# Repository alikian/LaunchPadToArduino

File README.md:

# LaunchPadToArduino
This a Arduino to LaunchPad adatper

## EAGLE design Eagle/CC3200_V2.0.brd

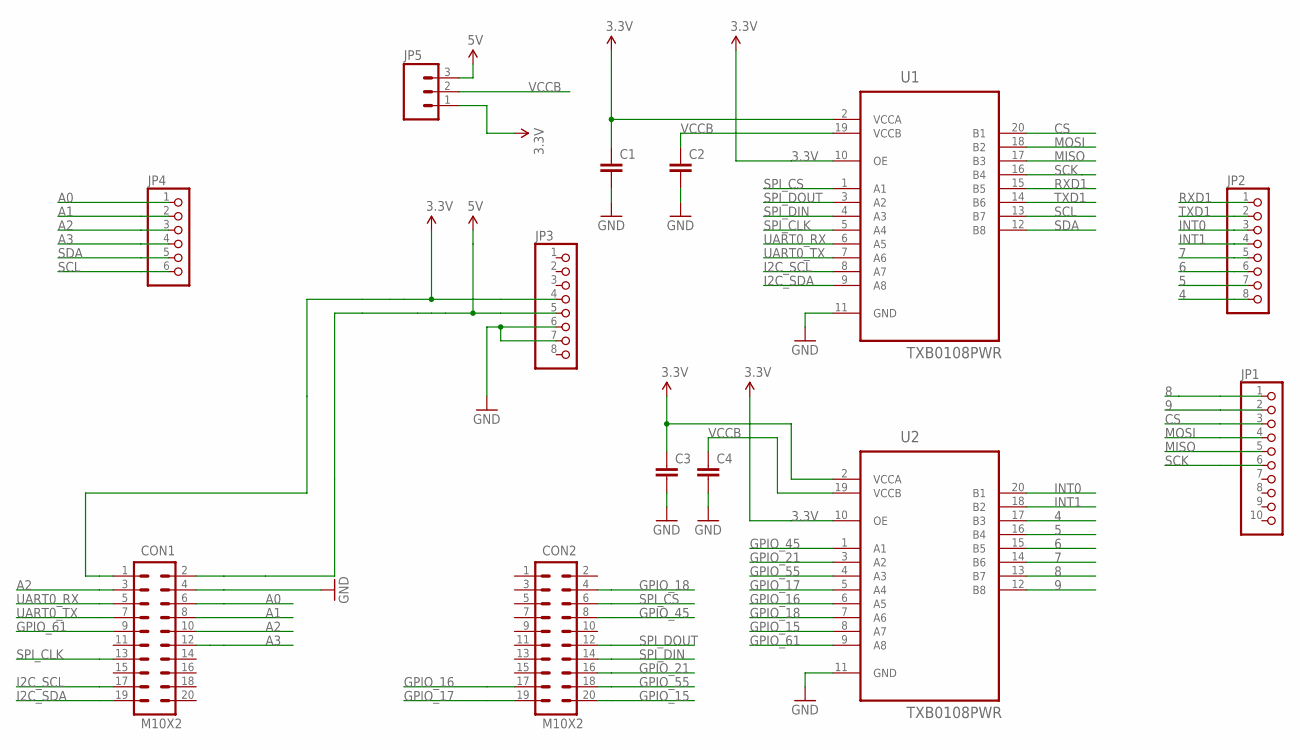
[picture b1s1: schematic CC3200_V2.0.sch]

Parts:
C1, C2, C3, C4: C-EUC0805; C0805
CON1, CON2: M10X2; 2X10
JP1: PINHD-1X10_ARD; 1X10
JP2, JP3: PINHD-1X8TH; 1X08-TH
JP4: PINHD-1X6TH; 1X06-TH
JP5: M03PTH; 1X03
U1, U2: TXB0108PWR; SOP65P640X120-20N

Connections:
3.3V: C1.1, C3.1, CON1.1, JP3.4, JP5.1, U1.2 (VCCA), U1.10 (OE), U2.2 (VCCA), U2.10 (OE)
4: JP2.8, U2.17 (B3)
5: JP2.7, U2.16 (B4)
5V: CON1.2, JP3.5, JP5.3
6: JP2.6, U2.15 (B5)
7: JP2.5, U2.14 (B6)
8: JP1.1, U2.13 (B7)
9: JP1.2, U2.12 (B8)
A0: CON1.6, JP4.1
A1: CON1.8, JP4.2
A2: CON1.3, CON1.10, JP4.3
A3: CON1.12, JP4.4
CS: JP1.3, U1.20 (B1)
GND: C1.2, C2.2, C3.2, C4.2, CON1.4, JP3.6, JP3.7, U1.11 (GND), U2.11 (GND)
GPIO_15: CON2.20, U2.8 (A7)
GPIO_16: CON2.17, U2.6 (A5)
GPIO_17: CON2.19, U2.5 (A4)
GPIO_18: CON2.4, U2.7 (A6)
GPIO_21: CON2.16, U2.3 (A2)
GPIO_45: CON2.8, U2.1 (A1)
GPIO_55: CON2.18, U2.4 (A3)
GPIO_61: CON1.9, U2.9 (A8)
I2C_SCL: CON1.17, U1.8 (A7)
I2C_SDA: CON1.19, U1.9 (A8)
INT0: JP2.3, U2.20 (B1)
INT1: JP2.4, U2.18 (B2)
MISO: JP1.5, U1.17 (B3)
MOSI: JP1.4, U1.18 (B2)
RXD1: JP2.1, U1.15 (B5)
SCK: JP1.6, U1.16 (B4)
SCL: JP4.6, U1.13 (B7)
SDA: JP4.5, U1.12 (B8)
SPI_CLK: CON1.13, U1.5 (A4)
SPI_CS: CON2.6, U1.1 (A1)
SPI_DIN: CON2.14, U1.4 (A3)
SPI_DOUT: CON2.12, U1.3 (A2)
TXD1: JP2.2, U1.14 (B6)
UART0_RX: CON1.5, U1.6 (A5)
UART0_TX: CON1.7, U1.7 (A6)
VCCB: C2.1, C4.1, JP5.2, U1.19 (VCCB), U2.19 (VCCB)

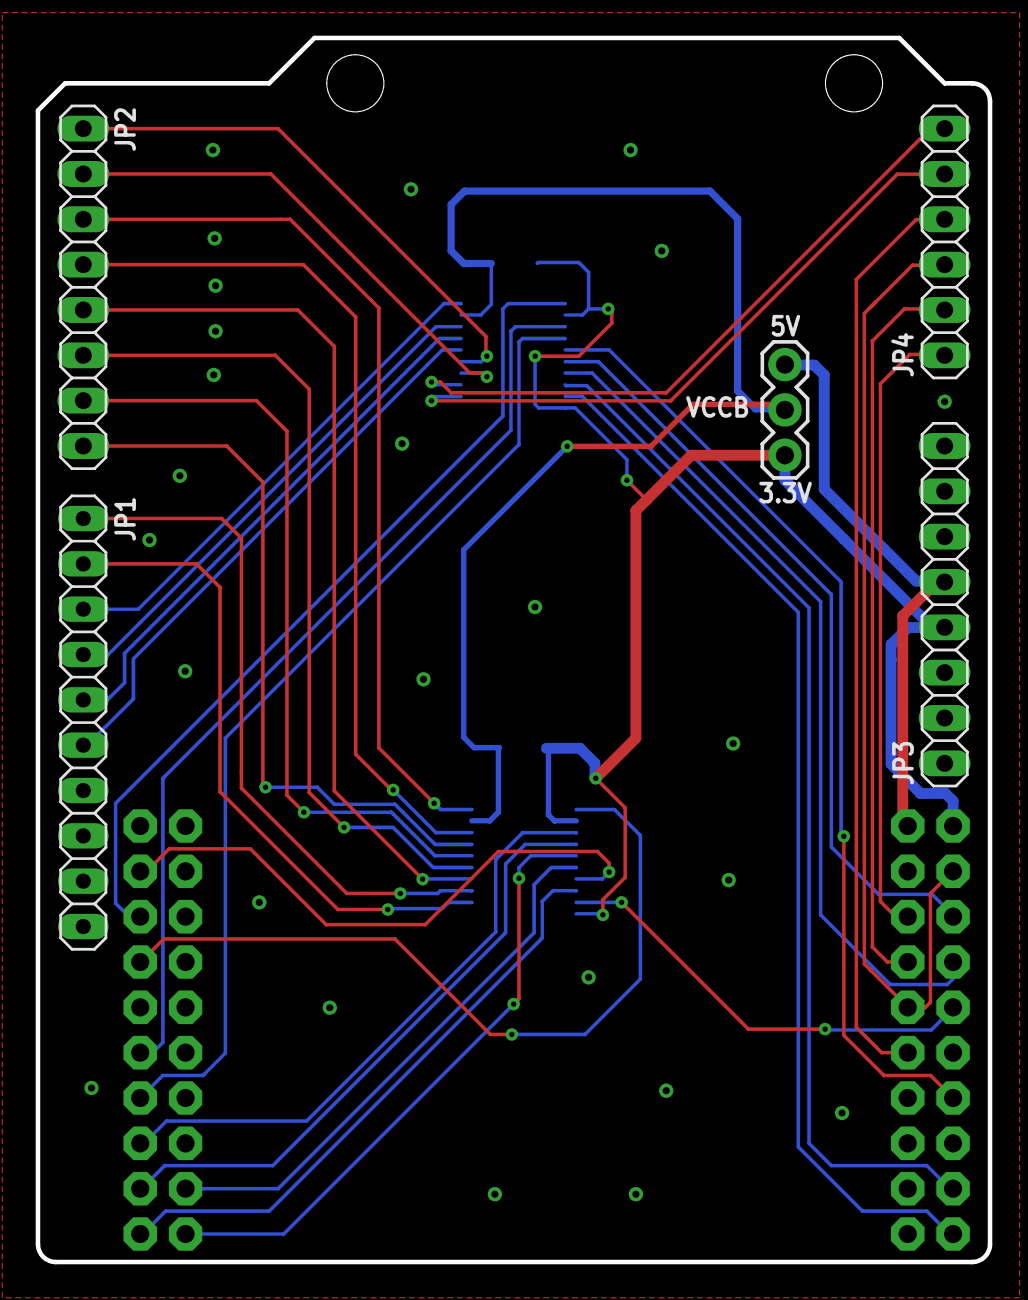
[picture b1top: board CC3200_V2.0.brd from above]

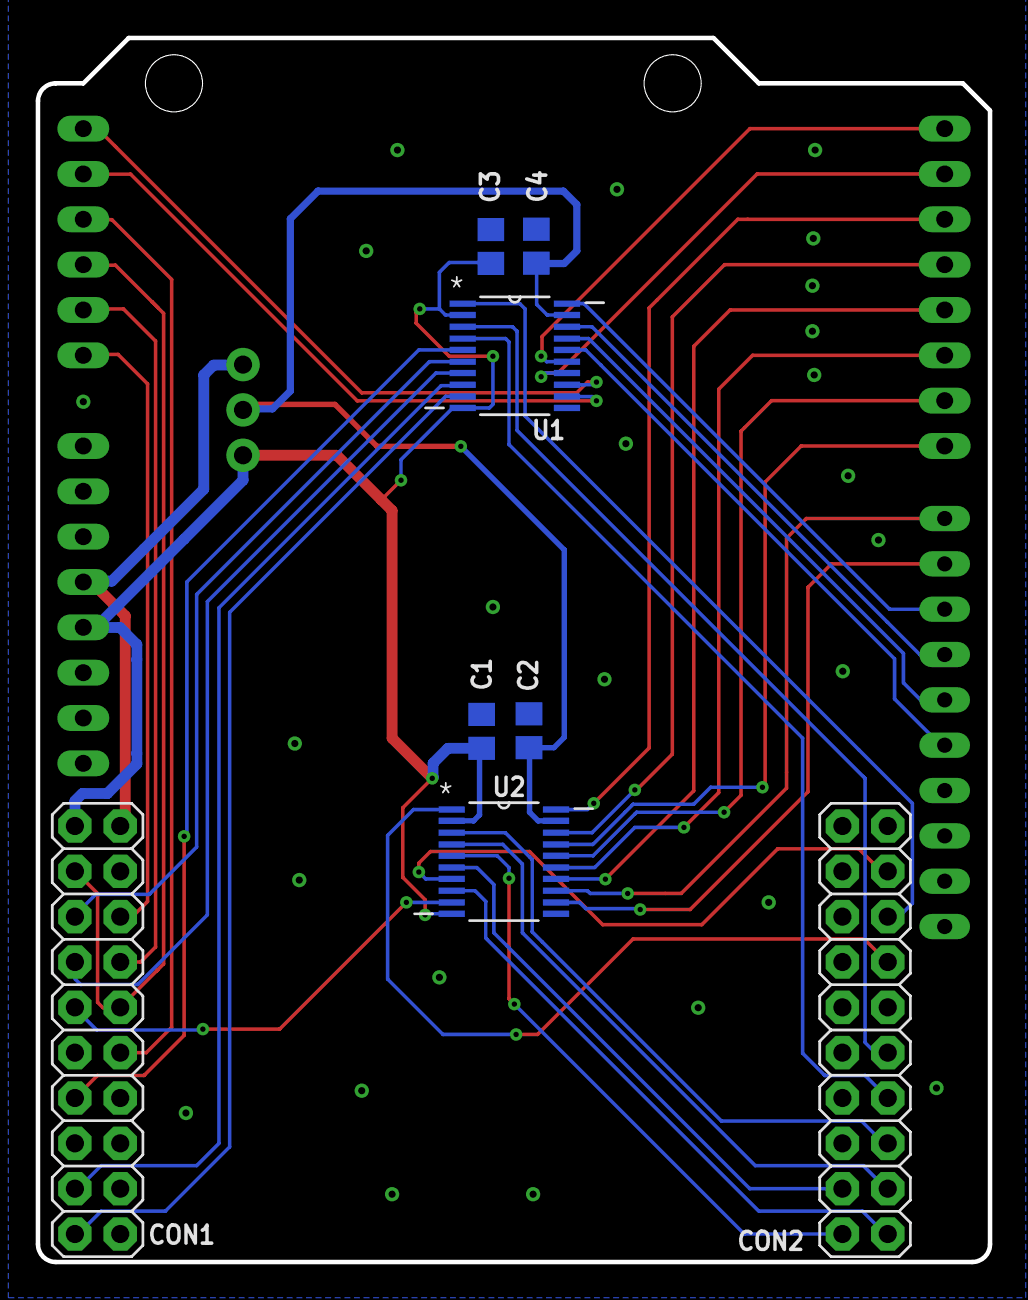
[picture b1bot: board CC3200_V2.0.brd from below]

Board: 2 copper layers, 53.3 x 68.6 mm, 13 parts (8 on the bottom side), 40 nets.

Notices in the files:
parts and their libraries:
SparkFun-Connectors: Licensing: CC v3.0 Share-Alike You are welcome to use this library for commercial purposes.
